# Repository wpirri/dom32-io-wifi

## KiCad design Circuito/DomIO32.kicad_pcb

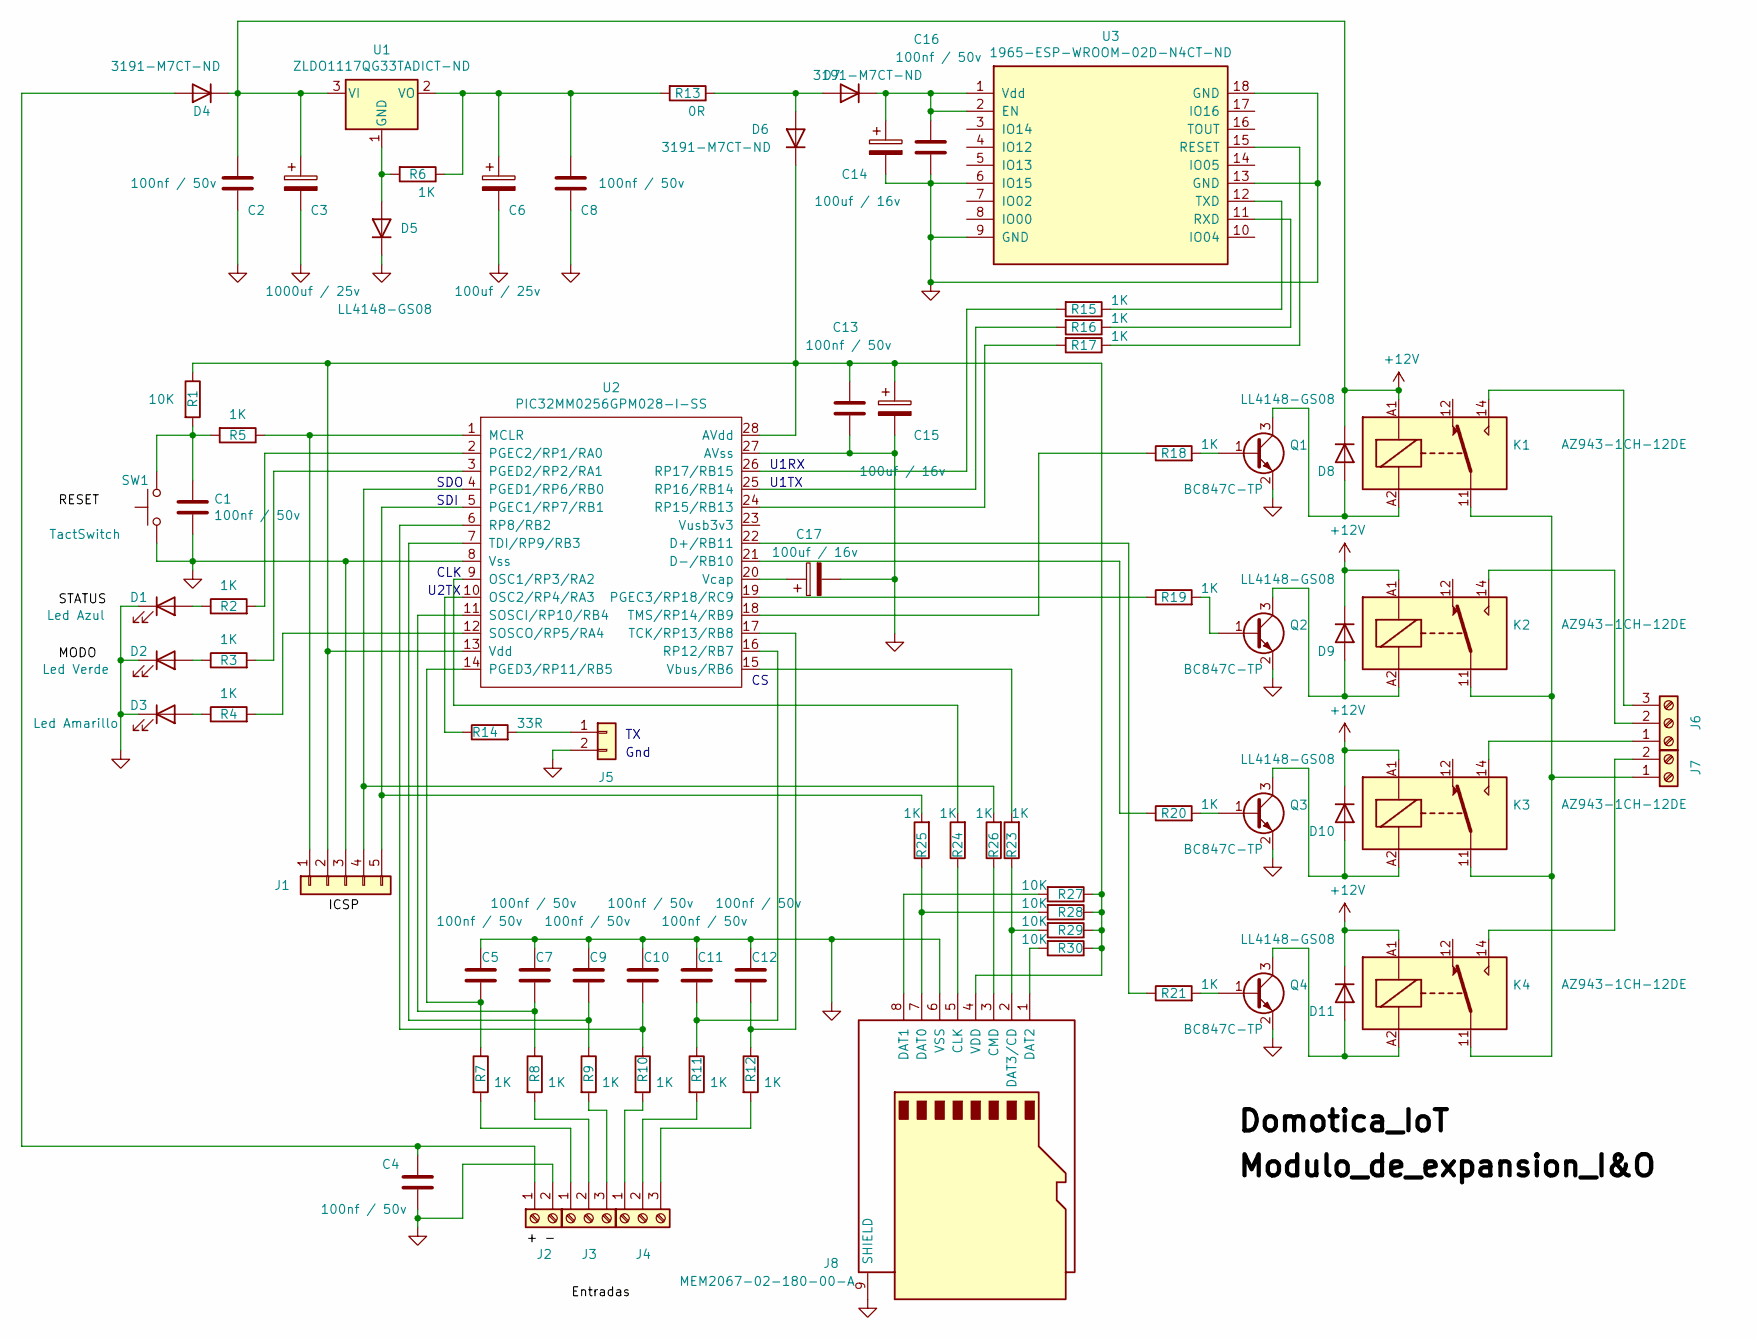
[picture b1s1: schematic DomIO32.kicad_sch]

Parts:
C1, C2, C4, C5, C7, C8, C9, C10, C11, C12, C13, C16: 100nf / 50v; C_0805_2012Metric_Pad1.18x1.45mm_HandSolder
C3: 1000uf / 25v; CP_Radial_D8.0mm_P5.00mm
C6: 100uf / 25v; CP_Radial_D6.3mm_P2.50mm
C14, C15, C17: 100uf / 16v; CP_Radial_D6.3mm_P2.50mm
D1: Led Azul; D_0805_2012Metric_Pad1.15x1.40mm_HandSolder
D2: Led Verde; D_0805_2012Metric_Pad1.15x1.40mm_HandSolder
D3: Led Amarillo; D_0805_2012Metric_Pad1.15x1.40mm_HandSolder
D4, D6, D7: 3191-M7CT-ND; D_SMA
D5, D8, D9, D10, D11: LL4148-GS08; D_SOD-128
J1: Poste X 5; PinHeader_1x05_P2.54mm_Vertical
J2, J7: 277-1667-ND; TerminalBlock_Phoenix_PT-1,5-2-5.0-H_1x02_P5.00mm_Horizontal
J3, J4, J6: 277-1578-ND; TerminalBlock_Phoenix_PT-1,5-3-5.0-H_1x03_P5.00mm_Horizontal
J5: Poste X 2; PinHeader_1x02_P2.54mm_Vertical
J8: MEM2067-02-180-00-A; microSD_HC_Wuerth_693072010801
K1, K2, K3, K4: AZ943-1CH-12DE; Relay_SPDT_Finder_36.11
Q1, Q2, Q3, Q4: BC847C-TP; SOT-23
R1, R27, R28, R29, R30: 10K; R_0805_2012Metric_Pad1.20x1.40mm_HandSolder
R2, R3, R4, R5, R6, R7, R8, R9, R10, R11, R12, R15, R16, R17, R18, R19, R20, R21, R23, R24, R25, R26: 1K; R_0805_2012Metric_Pad1.20x1.40mm_HandSolder
R13: 0R; R_0805_2012Metric_Pad1.20x1.40mm_HandSolder
R14: 33R; R_0805_2012Metric_Pad1.20x1.40mm_HandSolder
SW1: TactSwitch; SW_PUSH_6mm_H5mm
U1: ZLDO1117QG33TADICT-ND; SOT-223-3_TabPin2
U2: PIC32MM0256GPM028-I-SS; SSOP-28_5.3x10.2mm_P0.65mm
U3: 1965-ESP-WROOM-02D-N4CT-ND; ESP-WROOM-02

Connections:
+12V: C2.1, C3.1, D4.1 (K), D8.1 (K), D9.1 (K), D10.1 (K), D11.1 (K), K1.A1, K2.A1, K3.A1, K4.A1, U1.3 (VI)
GND: C1.2, C2.2, C3.2, C4.1, C5.1, C6.2, C7.1, C8.2, C9.1, C10.1, C11.1, C12.1, C13.2, C14.2, C15.2, C16.2, C17.2, D1.1 (K), D2.1 (K), D3.1 (K), D5.1 (K), J1.3, J2.2, J5.2, J8.6 (VSS), J8.9 (SHIELD), Q1.2 (E), Q2.2 (E), Q3.2 (E), Q4.2 (E), SW1.1, U2.8 (Vss), U2.27 (AVss), U3.6 (IO15), U3.9 (GND), U3.13 (GND), U3.18 (GND)
unnamed: C1.1, R1.2, R5.2, SW1.2
unnamed: D1.2 (A), R2.1
unnamed: D2.2 (A), R3.1
unnamed: D3.2 (A), R4.1
unnamed: C4.2, D4.2 (A), J2.1
unnamed: D5.2 (A), R6.2, U1.1 (GND)
unnamed: D6.2 (A), D7.2 (A), R13.1
unnamed: C13.1, C15.1, D6.1 (K), J1.2, J8.4 (VDD), R1.1, R27.1, R28.1, R29.1, R30.1, U2.13 (Vdd), U2.28 (AVdd)
unnamed: C14.1, C16.1, D7.1 (K), U3.1 (Vdd), U3.2 (EN)
unnamed: D8.2 (A), K1.A2, Q1.3 (C)
unnamed: D9.2 (A), K2.A2, Q2.3 (C)
unnamed: D10.2 (A), K3.A2, Q3.3 (C)
unnamed: D11.2 (A), K4.A2, Q4.3 (C)
unnamed: J1.1, R5.1, U2.1 (MCLR)
unnamed: J1.4, R26.2, U2.4 (PGED1/RP6/RB0)
unnamed: J1.5, R25.2, U2.5 (PGEC1/RP7/RB1)
unnamed: J3.1, R7.2
unnamed: J3.2, R8.2
unnamed: J3.3, R9.2
unnamed: J4.1, R10.2
unnamed: J4.2, R11.2
unnamed: J4.3, R12.2
unnamed: J5.1, R14.2
unnamed: J6.1, K3.14
unnamed: J6.2, K2.14
unnamed: J6.3, K1.14
unnamed: J7.1, K1.11, K2.11, K3.11, K4.11
unnamed: J7.2, K4.14
unnamed: J8.5 (CLK), R24.1
unnamed: J8.3 (CMD), R26.1
unnamed: J8.7 (DAT0), R25.1, R28.2
unnamed: J8.8 (DAT1), R27.2
unnamed: J8.1 (DAT2), R30.2
unnamed: J8.2 (DAT3/CD), R23.1, R29.2
unnamed: Q1.1 (B), R18.2
unnamed: Q2.1 (B), R19.2
unnamed: Q3.1 (B), R20.2
unnamed: Q4.1 (B), R21.2
unnamed: C6.1, C8.1, R6.1, R13.2, U1.2 (VO)
unnamed: R21.1, U2.22 (D+/RB11)
unnamed: R20.1, U2.21 (D-/RB10)
unnamed: R24.2, U2.9 (OSC1/RP3/RA2)
unnamed: R14.1, U2.10 (OSC2/RP4/RA3)
unnamed: R2.2, U2.2 (PGEC2/RP1/RA0)
unnamed: R19.1, U2.19 (PGEC3/RP18/RC9)
unnamed: R3.2, U2.3 (PGED2/RP2/RA1)
unnamed: C5.2, R7.1, U2.14 (PGED3/RP11/RB5)
unnamed: C10.2, R10.1, U2.6 (RP8/RB2)
unnamed: C11.2, R11.1, U2.16 (RP12/RB7)
unnamed: R17.2, U2.24 (RP15/RB13)
unnamed: R16.2, U2.25 (RP16/RB14)
unnamed: R15.2, U2.26 (RP17/RB15)
unnamed: C7.2, R8.1, U2.11 (SOSCI/RP10/RB4)
unnamed: R4.2, U2.12 (SOSCO/RP5/RA4)
unnamed: C12.2, R12.1, U2.17 (TCK/RP13/RB8)
unnamed: C9.2, R9.1, U2.7 (TDI/RP9/RB3)
unnamed: R18.1, U2.18 (TMS/RP14/RB9)
unnamed: R23.2, U2.15 (Vbus/RB6)
unnamed: C17.1, U2.20 (Vcap)
unnamed: R17.1, U3.15 (RESET)
unnamed: R16.1, U3.11 (RXD)
unnamed: R15.1, U3.12 (TXD)

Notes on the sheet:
U1TX
SDO
SDI
Gnd
U1RX
U2TX
CLK

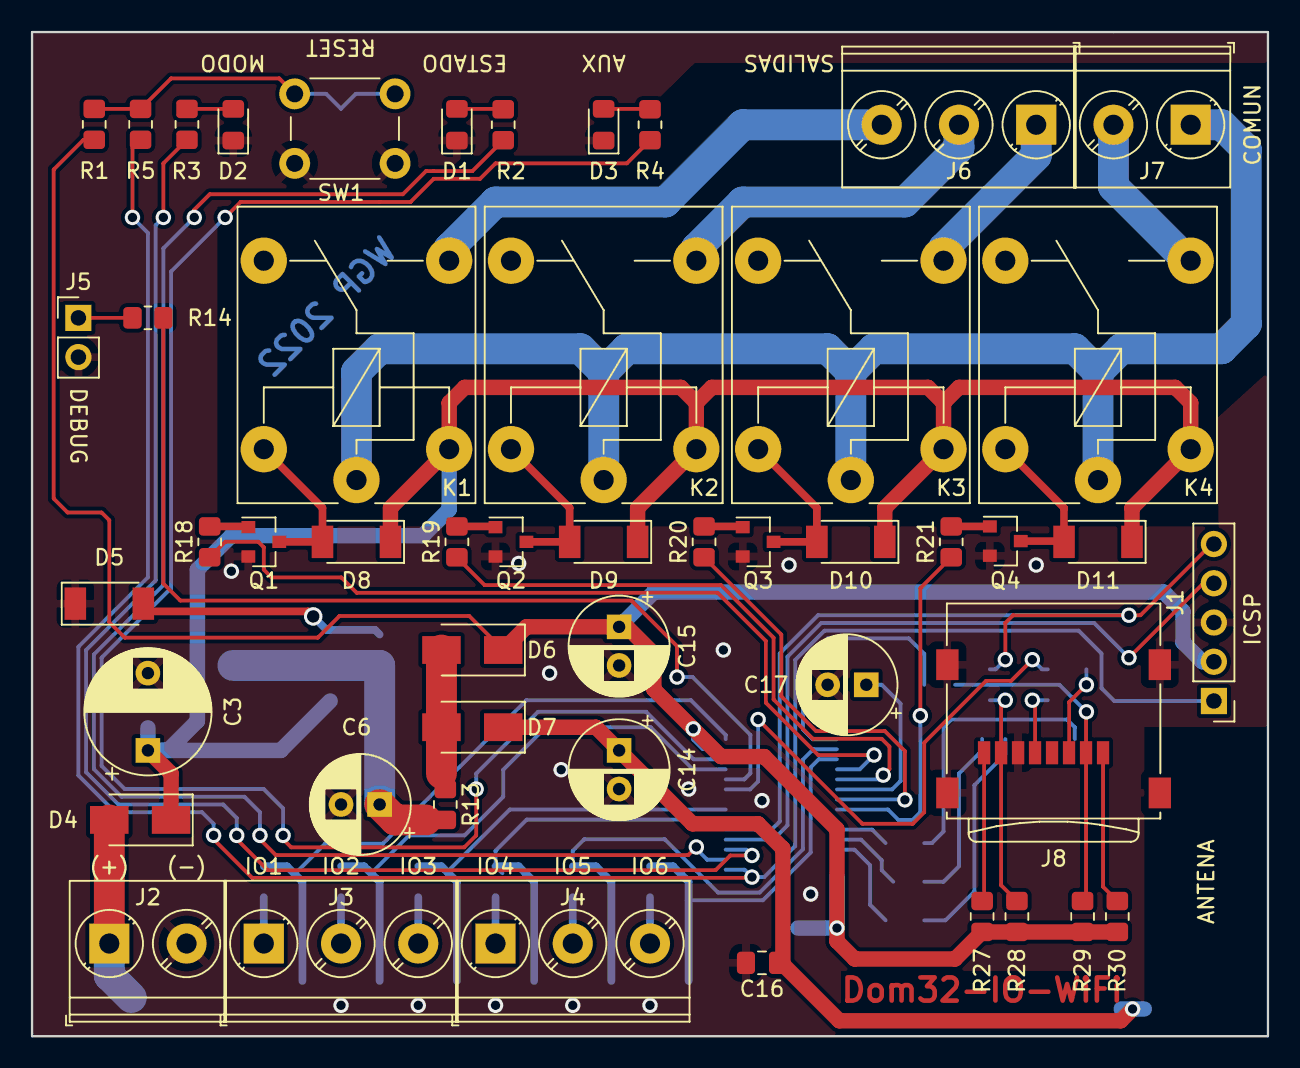
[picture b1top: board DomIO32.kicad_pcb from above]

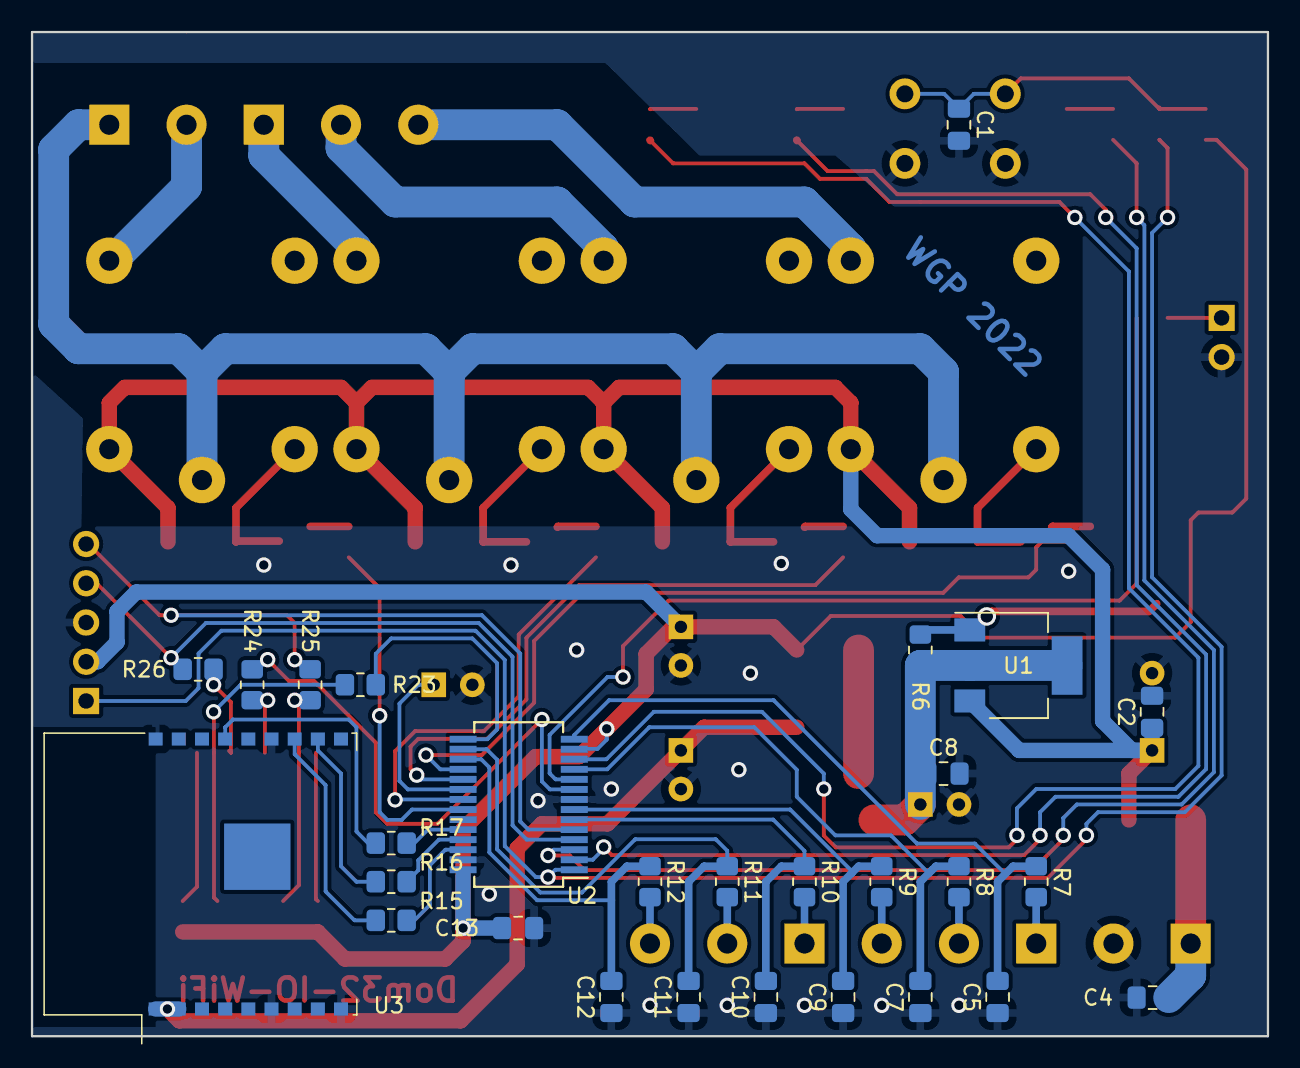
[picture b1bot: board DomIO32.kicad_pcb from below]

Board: 2 copper layers, 80.0 x 65.0 mm, 77 parts (28 on the bottom side), 64 nets.

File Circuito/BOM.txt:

"Component Count:","69"
"Ref","Qnty","Value","Cmp name","Footprint","Description","Vendor"
"C1, C2, C4, C5, C7, C8, C9, C10, C11, C12, C13, C16, ","12","100nf / 50v","C","Capacitor_SMD:C_0805_2012Metric_Pad1.18x1.45mm_HandSolder","Unpolarized capacitor",""
"C3, ","1","1000uf / 50v","C_Polarized","Capacitor_THT:CP_Radial_D8.0mm_P5.00mm","Polarized capacitor",""
"C6, C14, C15, C17, ","4","100uf / 16v","C_Polarized","Capacitor_THT:CP_Radial_D6.3mm_P2.50mm","Polarized capacitor",""
"D1, ","1","Led Azul","LED","Diode_SMD:D_0805_2012Metric_Pad1.15x1.40mm_HandSolder","Light emitting diode",""
"D2, ","1","Led Verde","LED","Diode_SMD:D_0805_2012Metric_Pad1.15x1.40mm_HandSolder","Light emitting diode",""
"D3, ","1","Led Amarillo","LED","Diode_SMD:D_0805_2012Metric_Pad1.15x1.40mm_HandSolder","Light emitting diode",""
"D4, D6, D7, ","3","M7","D","Diode_SMD:D_SMA","Diode",""
"D5, D8, D9, D10, D11, ","5","LL4148","D","Diode_SMD:D_SOD-128","Diode",""
"J1, ","1","Conector 1x5","Conn_01x05","Connector_PinHeader_2.54mm:PinHeader_1x05_P2.54mm_Vertical","Generic connector, single row, 01x05, script generated (kicad-library-utils/schlib/autogen/connector/)",""
"J2, J7, ","2","Bornera x2","Screw_Terminal_01x02","TerminalBlock_Phoenix:TerminalBlock_Phoenix_PT-1,5-2-5.0-H_1x02_P5.00mm_Horizontal","Generic screw terminal, single row, 01x02, script generated (kicad-library-utils/schlib/autogen/connector/)",""
"J3, J4, J6, ","3","Bornera x3","Screw_Terminal_01x03","TerminalBlock_Phoenix:TerminalBlock_Phoenix_PT-1,5-3-5.0-H_1x03_P5.00mm_Horizontal","Generic screw terminal, single row, 01x03, script generated (kicad-library-utils/schlib/autogen/connector/)",""
"J5, ","1","Conn_01x04","Conn_01x04","Connector_PinHeader_2.54mm:PinHeader_1x04_P2.54mm_Vertical","Generic connector, single row, 01x04, script generated (kicad-library-utils/schlib/autogen/connector/)",""
"K1, K2, K3, K4, ","4","FINDER-36.11","FINDER-36.11","Relay_THT:Relay_SPDT_Finder_36.11","FINDER 36.11, SPDT relay, 10A",""
"Q1, Q2, Q3, Q4, ","4","BC848","Q_NPN_BEC","Package_TO_SOT_SMD:SOT-23","NPN transistor, base/emitter/collector",""
"R1, ","1","10K","R","Resistor_SMD:R_0805_2012Metric_Pad1.20x1.40mm_HandSolder","Resistor",""
"R2, R3, R4, R5, R6, R7, R8, R9, R10, R11, R12, R15, R16, R17, R18, R19, R20, R21, ","18","1K","R","Resistor_SMD:R_0805_2012Metric_Pad1.20x1.40mm_HandSolder","Resistor",""
"R13, R14, R22, ","3","33R","R","Resistor_SMD:R_0805_2012Metric_Pad1.20x1.40mm_HandSolder","Resistor",""
"SW1, ","1","TactSwitch","SW_Push","Button_Switch_THT:SW_PUSH_6mm_H5mm","Push button switch, generic, two pins",""
"U1, ","1","ZLDO1117QG33TADICT-ND","LM1117-3.3","Package_TO_SOT_SMD:SOT-223-3_TabPin2","800mA Low-Dropout Linear Regulator, 3.3V fixed output, TO-220/TO-252/TO-263/SOT-223",""
"U2, ","1","PIC32MM0256GPM028-I-SS","PIC32MM0256GPM028-I-SS","Package_SO:SSOP-28_5.3x10.2mm_P0.65mm","",""
"U3, ","1","1965-ESP-WROOM-02D-N4CT-ND","ESP-02-DomIO32","RF_Module:ESP-WROOM-02","",""

MEM2067-02-180-00-A

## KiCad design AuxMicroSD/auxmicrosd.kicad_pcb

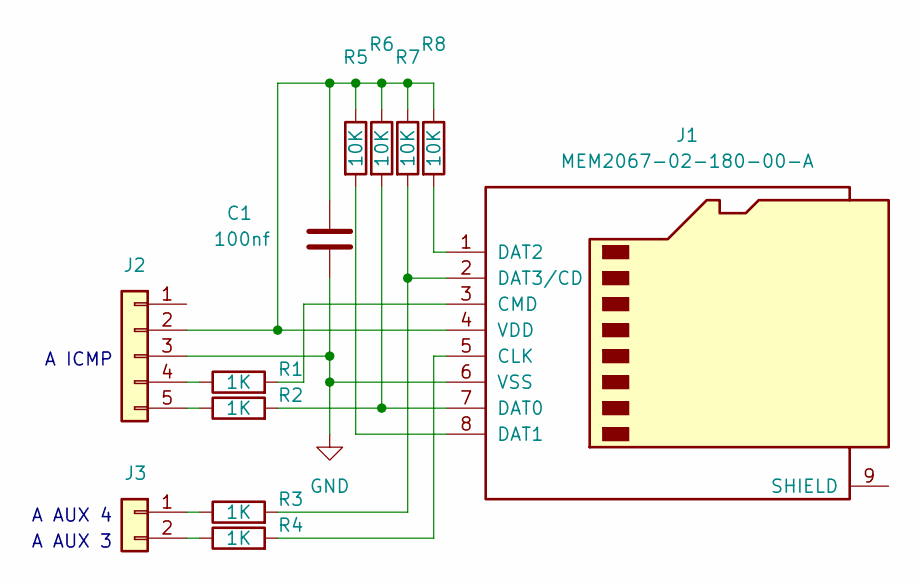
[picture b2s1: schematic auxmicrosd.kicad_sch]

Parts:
C1: 100nf; C_0805_2012Metric_Pad1.18x1.45mm_HandSolder
J1: MEM2067-02-180-00-A; microSD_HC_Wuerth_693072010801
J2: Poste X 5; PinHeader_1x05_P2.54mm_Vertical
J3: Poste X 2; PinHeader_1x02_P2.54mm_Vertical
R1, R2, R3, R4: 1K; R_0805_2012Metric_Pad1.20x1.40mm_HandSolder
R5, R6, R7, R8: 10K; R_0805_2012Metric_Pad1.20x1.40mm_HandSolder

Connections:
GND: C1.2, J1.6 (VSS), J2.3
unnamed: J1.5 (CLK), R4.2
unnamed: J1.3 (CMD), R1.2
unnamed: J1.7 (DAT0), R2.2, R6.2
unnamed: J1.8 (DAT1), R5.2
unnamed: J1.1 (DAT2), R8.2
unnamed: J1.2 (DAT3/CD), R3.2, R7.2
unnamed: C1.1, J1.4 (VDD), J2.2, R5.1, R6.1, R7.1, R8.1
unnamed: J2.4, R1.1
unnamed: J2.5, R2.1
unnamed: J3.1, R3.1
unnamed: J3.2, R4.1

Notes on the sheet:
A AUX 3
A AUX 4
A ICMP

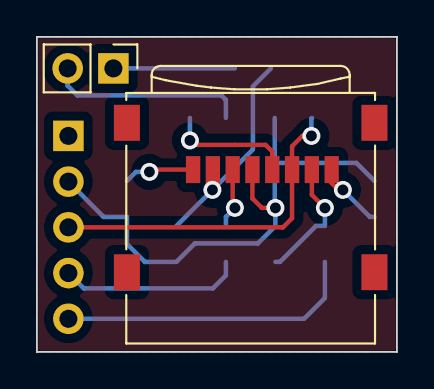
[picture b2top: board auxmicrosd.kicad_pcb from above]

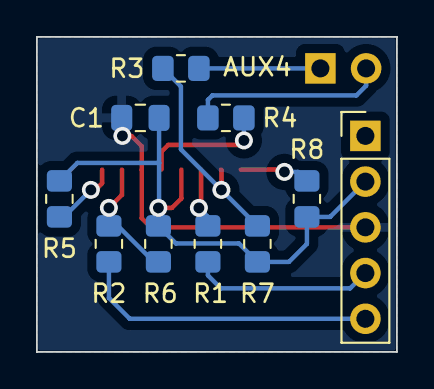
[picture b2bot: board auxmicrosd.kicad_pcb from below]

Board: 2 copper layers, 20.0 x 17.5 mm, 12 parts (10 on the bottom side), 12 nets.

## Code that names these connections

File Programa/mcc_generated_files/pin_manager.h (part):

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*/
/**
  @Summary
    Sets the GPIO pin, RA0, high using LATA0.

  @Description
    Sets the GPIO pin, RA0, high using LATA0.

  @Preconditions
    The RA0 must be set to an output.
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#define LED_Status_SetHigh()          ( LATASET = (1 << 0) )
/**
  @Summary
    Sets the GPIO pin, RA0, low using LATA0.

  @Description
    Sets the GPIO pin, RA0, low using LATA0.

  @Preconditions
    The RA0 must be set to an output.
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    Sets a value to the GPIO pin.

  @Description
    Sets or Resets the GPIO pin, RA0, low or high using LATA0.

  @Preconditions
    The RA0 must be set to an output.
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
/**
  @Summary
    Toggles the GPIO pin, RA0, using LATA0.

  @Description
    Toggles the GPIO pin, RA0, using LATA0.

  @Preconditions
    The RA0 must be set to an output.
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#define LED_Status_Toggle()           ( LATAINV = (1 << 0) )
/**
  @Summary
    Reads the value of the GPIO pin, RA0.

  @Description
    Reads the value of the GPIO pin, RA0.

  @Preconditions
    None.
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    </code>

*/
#define LED_Status_GetValue()         PORTAbits.RA0
/**
  @Summary
    Configures the GPIO pin, RA0, as an input.

  @Description
    Configures the GPIO pin, RA0, as an input.

  @Preconditions
    None.
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#define LED_Status_SetDigitalInput()   ( TRISASET = (1 << 0) )
/**
  @Summary
    Configures the GPIO pin, RA0, as an output.

  @Description
    Configures the GPIO pin, RA0, as an output.

  @Preconditions
    None.
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#define LED_Status_SetDigitalOutput()   ( TRISACLR = (1 << 0) )
/**
  @Summary
    Sets the GPIO pin, RA1, high using LATA1.

  @Description
    Sets the GPIO pin, RA1, high using LATA1.

  @Preconditions
    The RA1 must be set to an output.
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#define LED_Modo_SetHigh()          ( LATASET = (1 << 1) )
/**
  @Summary
    Sets the GPIO pin, RA1, low using LATA1.

  @Description
    Sets the GPIO pin, RA1, low using LATA1.

  @Preconditions
    The RA1 must be set to an output.
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    Sets a value to the GPIO pin.

  @Description
    Sets or Resets the GPIO pin, RA1, low or high using LATA1.

  @Preconditions
    The RA1 must be set to an output.
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
/**
  @Summary
    Toggles the GPIO pin, RA1, using LATA1.

  @Description
    Toggles the GPIO pin, RA1, using LATA1.

  @Preconditions
    The RA1 must be set to an output.
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#define LED_Modo_Toggle()           ( LATAINV = (1 << 1) )
/**
  @Summary
    Reads the value of the GPIO pin, RA1.

  @Description
    Reads the value of the GPIO pin, RA1.

  @Preconditions
    None.
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    </code>

*/
#define LED_Modo_GetValue()         PORTAbits.RA1
/**
  @Summary
    Configures the GPIO pin, RA1, as an input.

  @Description
    Configures the GPIO pin, RA1, as an input.

  @Preconditions
    None.
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#define LED_Modo_SetDigitalInput()   ( TRISASET = (1 << 1) )
/**
  @Summary
    Configures the GPIO pin, RA1, as an output.

  @Description
    Configures the GPIO pin, RA1, as an output.

  @Preconditions
    None.
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#define LED_Modo_SetDigitalOutput()   ( TRISACLR = (1 << 1) )
/**
  @Summary
    Sets the GPIO pin, RA2, high using LATA2.

  @Description
    Sets the GPIO pin, RA2, high using LATA2.

  @Preconditions
    The RA2 must be set to an output.
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#define SPI_SCK_SetHigh()          ( LATASET = (1 << 2) )
/**
  @Summary
    Sets the GPIO pin, RA2, low using LATA2.

  @Description
    Sets the GPIO pin, RA2, low using LATA2.

  @Preconditions
    The RA2 must be set to an output.
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    Sets a value to the GPIO pin.

  @Description
    Sets or Resets the GPIO pin, RA2, low or high using LATA2.

  @Preconditions
    The RA2 must be set to an output.
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
/**
  @Summary
    Toggles the GPIO pin, RA2, using LATA2.

  @Description
    Toggles the GPIO pin, RA2, using LATA2.

  @Preconditions
    The RA2 must be set to an output.
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#define SPI_SCK_Toggle()           ( LATAINV = (1 << 2) )
/**
  @Summary
    Reads the value of the GPIO pin, RA2.

  @Description
    Reads the value of the GPIO pin, RA2.

  @Preconditions
    None.
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    </code>

*/
#define SPI_SCK_GetValue()         PORTAbits.RA2
/**
  @Summary
    Configures the GPIO pin, RA2, as an input.

  @Description
    Configures the GPIO pin, RA2, as an input.

  @Preconditions
    None.
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#define SPI_SCK_SetDigitalInput()   ( TRISASET = (1 << 2) )
/**
  @Summary
    Configures the GPIO pin, RA2, as an output.

  @Description
    Configures the GPIO pin, RA2, as an output.

  @Preconditions
    None.
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#define SPI_SCK_SetDigitalOutput()   ( TRISACLR = (1 << 2) )
/**
  @Summary
    Sets the GPIO pin, RA4, high using LATA4.

  @Description
    Sets the GPIO pin, RA4, high using LATA4.

  @Preconditions
    The RA4 must be set to an output.
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#define LED_Aux_SetHigh()          ( LATASET = (1 << 4) )
/**
  @Summary
    Sets the GPIO pin, RA4, low using LATA4.

  @Description
    Sets the GPIO pin, RA4, low using LATA4.

  @Preconditions
    The RA4 must be set to an output.
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    Sets a value to the GPIO pin.

  @Description
    Sets or Resets the GPIO pin, RA4, low or high using LATA4.

  @Preconditions
    The RA4 must be set to an output.
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
/**
  @Summary
    Toggles the GPIO pin, RA4, using LATA4.

  @Description
    Toggles the GPIO pin, RA4, using LATA4.

  @Preconditions
    The RA4 must be set to an output.
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#define LED_Aux_Toggle()           ( LATAINV = (1 << 4) )
/**
  @Summary
    Reads the value of the GPIO pin, RA4.

  @Description
    Reads the value of the GPIO pin, RA4.

  @Preconditions
    None.
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    </code>

*/
#define LED_Aux_GetValue()         PORTAbits.RA4
/**
  @Summary
    Configures the GPIO pin, RA4, as an input.

  @Description
    Configures the GPIO pin, RA4, as an input.

  @Preconditions
    None.
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#define LED_Aux_SetDigitalInput()   ( TRISASET = (1 << 4) )
/**
  @Summary
    Configures the GPIO pin, RA4, as an output.

  @Description
    Configures the GPIO pin, RA4, as an output.

  @Preconditions
    None.
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#define LED_Aux_SetDigitalOutput()   ( TRISACLR = (1 << 4) )
/**
  @Summary
    Sets the GPIO pin, RB0, high using LATB0.

  @Description
    Sets the GPIO pin, RB0, high using LATB0.

  @Preconditions
    The RB0 must be set to an output.
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#define SPI_SDO_SetHigh()          ( LATBSET = (1 << 0) )
/**
  @Summary
    Sets the GPIO pin, RB0, low using LATB0.

  @Description
    Sets the GPIO pin, RB0, low using LATB0.

  @Preconditions
    The RB0 must be set to an output.
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    Sets a value to the GPIO pin.

  @Description
    Sets or Resets the GPIO pin, RB0, low or high using LATB0.

  @Preconditions
    The RB0 must be set to an output.
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
/**
  @Summary
    Toggles the GPIO pin, RB0, using LATB0.

  @Description
    Toggles the GPIO pin, RB0, using LATB0.

  @Preconditions
    The RB0 must be set to an output.
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#define SPI_SDO_Toggle()           ( LATBINV = (1 << 0) )
/**
  @Summary
    Reads the value of the GPIO pin, RB0.

  @Description
    Reads the value of the GPIO pin, RB0.

  @Preconditions
    None.
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    </code>

*/
#define SPI_SDO_GetValue()         PORTBbits.RB0
/**
  @Summary
    Configures the GPIO pin, RB0, as an input.

  @Description
    Configures the GPIO pin, RB0, as an input.

  @Preconditions
    None.
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#define SPI_SDO_SetDigitalInput()   ( TRISBSET = (1 << 0) )
/**
  @Summary
    Configures the GPIO pin, RB0, as an output.

  @Description
    Configures the GPIO pin, RB0, as an output.

  @Preconditions
    None.
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#define SPI_SDO_SetDigitalOutput()   ( TRISBCLR = (1 << 0) )
/**
  @Summary
    Sets the GPIO pin, RB1, high using LATB1.

  @Description
    Sets the GPIO pin, RB1, high using LATB1.

  @Preconditions
    The RB1 must be set to an output.
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#define SPI_SDI_SetHigh()          ( LATBSET = (1 << 1) )
/**
  @Summary
    Sets the GPIO pin, RB1, low using LATB1.

  @Description
    Sets the GPIO pin, RB1, low using LATB1.

  @Preconditions
    The RB1 must be set to an output.
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    Sets a value to the GPIO pin.

  @Description
    Sets or Resets the GPIO pin, RB1, low or high using LATB1.

  @Preconditions
    The RB1 must be set to an output.
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
/**
  @Summary
    Toggles the GPIO pin, RB1, using LATB1.

  @Description
    Toggles the GPIO pin, RB1, using LATB1.

  @Preconditions
    The RB1 must be set to an output.
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#define SPI_SDI_Toggle()           ( LATBINV = (1 << 1) )
/**
  @Summary
    Reads the value of the GPIO pin, RB1.

  @Description
    Reads the value of the GPIO pin, RB1.

  @Preconditions
    None.
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    </code>

*/
#define SPI_SDI_GetValue()         PORTBbits.RB1
/**
  @Summary
    Configures the GPIO pin, RB1, as an input.

  @Description
    Configures the GPIO pin, RB1, as an input.

  @Preconditions
    None.
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#define SPI_SDI_SetDigitalInput()   ( TRISBSET = (1 << 1) )
/**
  @Summary
    Configures the GPIO pin, RB1, as an output.

  @Description
    Configures the GPIO pin, RB1, as an output.

  @Preconditions
    None.
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#define SPI_SDI_SetDigitalOutput()   ( TRISBCLR = (1 << 1) )
/**
  @Summary
    Sets the GPIO pin, RB10, high using LATB10.

  @Description
    Sets the GPIO pin, RB10, high using LATB10.

  @Preconditions
    The RB10 must be set to an output.
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#define OUT3_SetHigh()          ( LATBSET = (1 << 10) )
/**
  @Summary
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
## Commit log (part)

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2020-10-19 Reacondicionamiento base.
    Por el tamaño del procesador se decide no utilizar colas que requieren alocación dinamica de memoria. Se elimina el código asociado y se vuelven a generar los modulos con Code Congurator.
2020-10-21 Avance
    Avance: Desarrollo de interface con modulo wifi
2020-10-22 Correccion
    Se agrega la conexion del pin 6 del modulo wifi
2020-10-22 AT -> OK
    Se agrega limpieza del buffer de entrada serial y reconocimiento de las respuesta OK
2020-11-05 WiFi Init
    Secuencia de inicializacion WiFi funcionando. Arranca en modo AP esperando aceptando conexion sin passsord por 60 segundos. El led de status indica conexi[on y a que AP el led de modo indica si est;a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
2020-11-07 Formulario
    Implementada la configuracion Wifi desde formulario
2020-11-07 Leds diferidos
    Se difiere el momento en que titilan los leds para facilitar la interpretación
2020-11-09 Flash Ok
    Configuración en flash Ok
    Se agrega No Solicitado de captura de version de firmware, Sin terminar.
2020-11-09 Correcciones flash
    Correcciones a la implementaci[on de la configuracipn den flash
2020-11-11 Control
    ensajeria y manejo de modo y estado de la interface
2020-11-16 Notificacion
    Mensaje de notificacion a central por medio de un POST
2020-11-16 Finde linea
    Cambios en la deteccion de fin de linea para diferenciar comandos de stream
2020-11-18 Mejoras web
    Mejoras en la comunicacion web, espera en el close y mejorada la deteccion de fin de lineas y/o stream.
    Cambios en la secuencia de inicio, los leds se alternan hasta que arranca el modulo wifi.
2020-11-22 IO Expansion
    Configuracion y controlde puerto de expansion
    Contrl de pull-up en entradas
2020-12-08 Encapsulado PIC
    Correcciones al encapsulado del PIC
2020-12-08 Pre SSL
    Preparacion para SSL
2020-12-10 Formularios de configuracion y control
    Se agregan formularios para configuración de puertos y gestion de estados
2020-12-19 Reintento de notificacion
    Se agrega una modificacion para que reinente el envío de notificación si no se encontró un slot libre para cargar el mensaje en la cola circular.
2020-12-19 Correccion en notificacion
    Se corrije el modo de setear las notificaciones por cambios de estado
2021-03-13 dht11 y Wiegand
    Se agregan las funcionalidades de interface con sensor de temperatura y humedad dht11 y lector de tarjetas wiegand
2021-03-13 Nueva doc
    Se agrega documentación de diseño
2021-05-01 Update http.c
    Interface http ampliada. Se agregan consultas de estados, configuración de puertos y configuracion de wifi con mensajeria de servicios web sin formularios.
2021-07-26 Comando Switch
    Se agrega el comando switch que cambia el estado de los puertos seleccionados
2021-11-30 Se corrige capacitor electrolitico para nuevas librerias
    Se corrige capacitor electrolitico para nuevas librerias
2021-11-30 PIC32MM0256GPM028
    PIC32MM0256GPM028
2021-12-13 Eliminado
    Eliminadp
2022-02-21 Nuevo circuito co relees
    Nuevo circuito co relees
2022-02-27 Reestructuracion del proyecto
    Reestructuracion del proyecto
2022-03-06 Modulo wifi implementado por serial con cola en recepcion
    Modulo wifi implementado por serial con cola en recepcion
2022-03-07 Formulario de configuracion
    Formulario de configuracion
2022-03-11 Correccion del core timer
    Correccion del core timer
2022-03-12 Revert "Correccion del core timer"
    This reverts commit e15d4be750ec0100916b0a144cfc09ea950c0574.
2022-03-12 Revert "Uso del PLL"
    This reverts commit 0cf0e143c8710c0b307ed75abef17277179103a8.
2022-03-13 Correcciones varias
    Correcciones varias
2022-03-14 Correccion en queue clean
    Correccion en queue clean
2022-03-16 Vuelta al viejo esquema
    Vuelta al viejo esquema
2022-03-16 Funcionando nuevamente y ahora con debug al serial
    Funcionando nuevamente y ahora con debug al serial
2022-03-17 Debug de mensajeria http
    Debug de mensajeria http
2022-03-18 Update
    Configuracion de 6 IO y 4 OUT
2022-03-19 PCB
    PCB
2022-03-21 Antes de agregar areas de relleno
    Antes de agregar areas de relleno
2022-03-22 Final PCB
    Final PCB
2022-03-28 Correcciones previo fabricación
    Correcciones previo fabricación
2022-04-03 Se agrega el gabinete
    Se agrega el gabinete
2022-04-24 Correcciones de puesta en marcha de placa nueva
    Correcciones de puesta en marcha de placa nueva
2022-04-24 Logo en el gabinete
    Logo en el gabinete
2022-04-25 Se saca control de led aux por trafico
    Se saca control de led aux por trafico
2022-04-25 Se agrega funcionalidad de pulso
    Se agrega funcionalidad de pulso
2022-05-07 Desactivacion rapida de logueo y se deja de borrar cualquier mensaje entrante del serial RX del modem cuando se escribe algo para el TX
    Desactivacion rapida de logueo y se deja de borrar cualquier mensaje entrante del serial RX del modem cuando se escribe algo para el TX
2022-05-18 Conversion de caracteres de escape en formularios
    Conversion de caracteres de escape en formularios
2022-05-18 Titila el led AUX cuando está en linea con la central
    Titila el led AUX cuando está en linea con la central
2022-05-19 Retraso en el control de cambios para evitar transmitir cambios cuando arranca y cuando actualiza configuración
    Retraso en el control de cambios para evitar transmitir cambios cuando arranca y cuando actualiza configuración
2022-05-20 Se acorta el ojo de buey
    Se acorta el ojo de buey
2022-05-23 Definición de flags para https, wiegand y dht11
    Definición de flags para https, wiegand y dht11
2022-05-25 Soporte Wiegand
    Soporte Wiegand
2022-05-30 Circuito completo de temperatura y humedad
    Circuito completo de temperatura y humedad
2022-06-07 Archivos de la placa vieja
    Archivos de la placa vieja
2022-06-07 Se agregan las orejas de fijacion para tornillos
    Se agregan las orejas de fijacion para tornillos
2022-06-07 Tapa con logo en dos colores
    Tapa con logo en dos colores
2022-06-10 Entradas analogicas
    Entradas analogicas
2022-06-16 Solo permitir configuracion analogica en las entradas que lo soportan
    Solo permitir configuracion analogica en las entradas que lo soportan
2022-06-28 Cambio en el formato de transmitir estados
    Cambio en el formato de transmitir estados
2022-09-01 Reconexion en caso de errores cosecutivos
    Reconexion en caso de errores cosecutivos
2022-09-06 Correcciones a reinicio de conexion
    Correcciones a reinicio de conexion
2022-09-06 Tapa en dos colores OK
    Color 1: Blanco, Color2: Negro
2022-10-06 Gabinete con Serigrafia
    Gabinete con Serigrafia
2022-10-07 Logueo, RTCC y optimización de comm
    Se agrega LogMessage como funcion que agrega la hora al log por consola. Se agrega el RTCC. Falta sincronizar hora.
2022-11-08 Actualizacion de la documentacion
    Actualizacion de la documentacion
2022-11-08 Mejora en tiempo de respuesta
    Mejora en tiempo de respuesta
2022-12-01 Correccion de respuesta a solicitudes de cambio de estado de IO y OUT
    Correccion de respuesta a solicitudes de cambio de estado de IO y OUT
2022-12-03 Correcciones de pulso
    Correcciones de pulso
2022-12-08 Cambio en delay para SHT para que funcione con codigo optimizado
    Cambio en delay para SHT para que funcione con codigo optimizado
2022-12-23 Se agrega script para crear codigos QR
    Se agrega script para crear codigos QR
2022-12-23 Correccion de lectura de tarjeta
    Correccion de lectura de tarjeta
2022-12-28 Soporte para modulos WiFi viejos y SSL
    Soporte para modulos WiFi viejos y SSL
2022-12-29 Falla
    Falla
2022-12-29 Vuelta atras por errores
    Vuelta atras por errores
2022-12-30 Correcciones en maquinas de estados
    Correcciones en maquinas de estados
2023-01-16 Componentes actualizados
    Regulador 3v3 que soporta Vin de 18V
    ESP-02 Version nueva
2023-01-23 Datos de Firmware en mensajes de estado y cambios de estado
    Datos de Firmware en mensajes de estado y cambios de estado
2023-01-24 Se alarga el pulsador
    Se alarga el pulsador
2023-02-07 Autodetect de sensor DHT
    Autodetect de sensor DHT
2023-02-07 Cambio en resistencia 22R por 33R
    Cambio en resistencia 22R por 33R
2023-02-08 Se elimina la optimización en estas dos funciones que provocan error en la comunicación con el ESP-02
    Se elimina la optimización en estas dos funciones que provocan error en la comunicación con el ESP-02
2023-02-10 Se limita el acceso a la página de configuración solo mientras está encendido el AP
    Se limita el acceso a la página de configuración solo mientras está encendido el AP
2023-02-10 Se eliminan funciones no usadas de las funciones autogeneradas.
    Se eliminan funciones no usadas de las funciones autogeneradas.
2023-02-10 Se agrega un delay en la escritura del buffer serial
    Se agrega un delay en la escritura del buffer serial
2023-02-14 Se elimina la desabilitación de interrupciones en funciones de DHT
    Se elimina la desabilitación de interrupciones en funciones de DHT
2023-02-14 Revert "Autodetect de sensor DHT"
    This reverts commit 9b306b6f970464da3af8964a75de3c61d7096483.
2023-02-14 Se vuelve atras la deteccion automatica de DHT
2023-04-25 Se agrega mensajeria
    Se agrega mensajeria
2024-02-05 Proyecto actualizado a MPLAB X IDE 6.20
    Proyecto actualizado a MPLAB X IDE 6.20
2024-02-13 Se agregan datos en el mensaje e estado
    Se agrega en el mensaje de estado TYP=IO para diferenciarlo de IR y de PI.
    Se agrega en el mensaje de estado SSL y YES / NO dependiendo del soporte para SSL en el modulo Wifi
2024-03-06 Mejoras
    Mejoras
2024-03-08 Mejoras on-line
    Se agrega analisis de la respuesta para detectar errores de HTML y del sistema
2024-03-20 Comparacion de estado en la respuesta
    Comparacion de estado en la respuesta
2024-03-28 Colas de mensajes contra modulo wifi mejoradas
    Colas de mensajes contra modulo wifi mejoradas
2024-04-01 Mejora en sincronización de hora
    Mejora en sincronización de hora
2024-04-03 RTCC corregido
    RTCC corregido
2024-04-08 Mapeo de pines para SPI2
    Mapeo de pines para SPI2
2024-04-09 SD Funcionando
    SD Funcionando
2024-04-14 Configuracion en SD
    Configuracion en SD
2024-04-15 SD Ok
    SD Ok
2024-05-03 No se borra el programa de la SD
    No se borra el programa de la SD
2024-05-03 UPDATE-FW
    UPDATE-FW
2024-05-08 Implementado Download de Formware y RESET para su carga
    Implementado Download de Formware y RESET para su carga
2024-05-11 Backup de config en flash
    Backup de config en flash
2024-05-13 Mejoras flash / SD
    Se inhibe la lectura y escritura de configuracion y el download cuando no se detecta la tarjeta SD
2024-06-20 MicroSD agregada
    MicroSD agregada
2024-06-28 Vuelta atras ara estabilizar
    Vuelta atras ara estabilizar
2024-07-30 Correcciones de update de firmware y configuracion
    Correcciones de update de firmware y configuracion
2024-11-25 Mejoras WiFi
    Se acorta el tiempo de inicio del modulo wifi
    Se cambia la forma de inicio para que saltee el modo cnofigracion
    Se mejora la transferencia de archivo
2024-11-26 Mejoras en la inicializacion WiFi
    Mejoras en la inicializacion WiFi
2024-11-28 Mejoras en WiFi, Http y Upgrade
    Mejoras en WiFi, Http y Upgrade
2024-12-02 Compatibilidad de configuración
    Soporte para cambios en tamaño de archivo de configuración sin perder los datos
2025-01-07 Mejoras en download
    Mejoras en download actualizadas desde modulo touch
2025-01-09 Correccion en manejo de comunicacion
    Correccion en manejo de comunicacion
2025-04-19 Conreol de IP de WiFi
    Conreol de IP de WiFi
2025-04-23 Correcciones en WiFi
    Correcciones en WiFi
2025-06-06 Control para evitar errores en pulso
    Control para evitar errores en pulso
2025-09-28 Comando para reset y Update de firmware
    Comando para reset y Update de firmware
2025-09-29 Code Refresh
    Actualización después de una vuelta atrás y reimpacto de modificaciones con correccion de algunos errores en el uso de los flags de conexión
2025-10-03 Vuelta a tras de algunos cambios que rompian el download
    Vuelta a tras de algunos cambios que rompian el download
2025-10-04 Se actualiza con cambios en firmware de touch
    Se actualiza con cambios en firmware de touch
2025-10-09 Control de integridad de archivo bajado
    Control de integridad de archivo bajado

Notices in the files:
Programa/mcc_generated_files/pin_manager.h:
(c) 2020 Microchip Technology Inc. and its subsidiaries. You may use this
